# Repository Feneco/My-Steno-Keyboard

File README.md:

# My-Steno-Keyboard
A small stenography keyboard project, including kicad files

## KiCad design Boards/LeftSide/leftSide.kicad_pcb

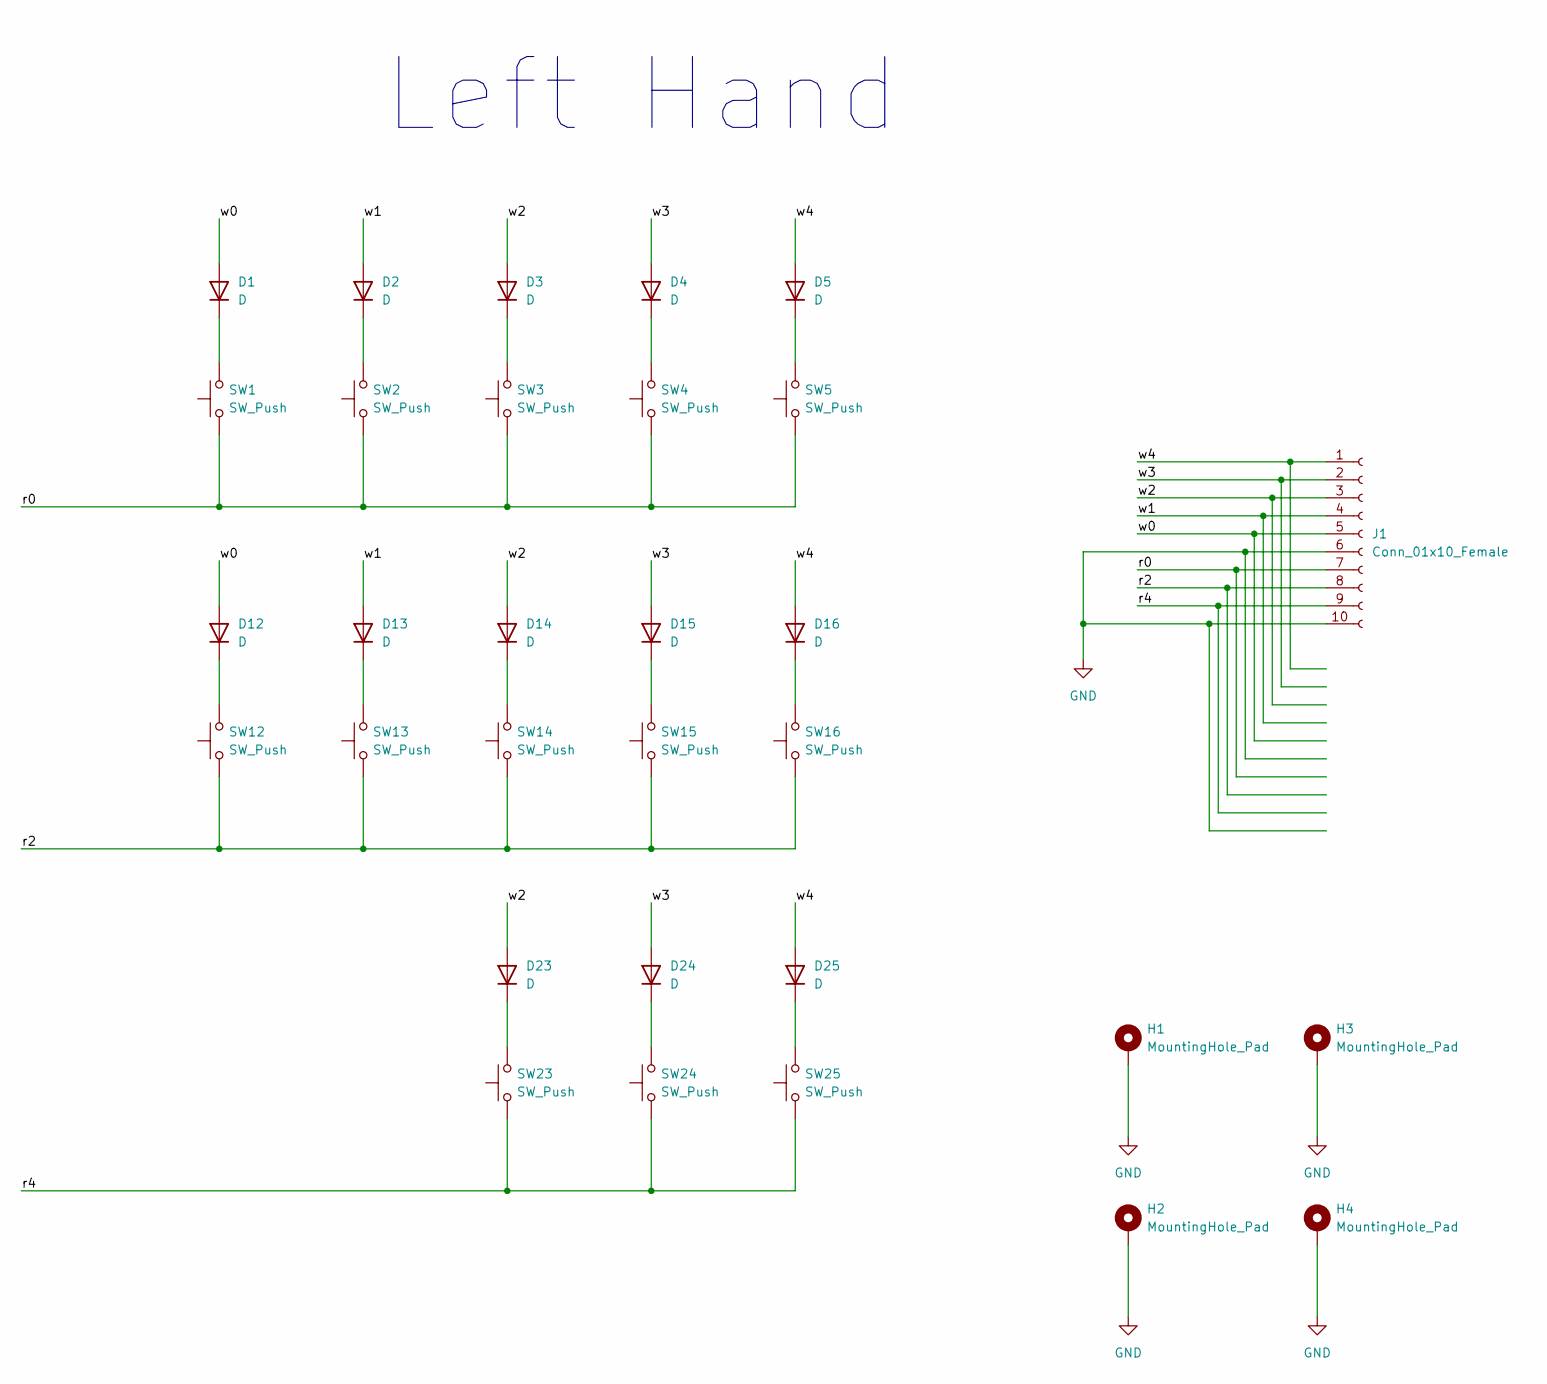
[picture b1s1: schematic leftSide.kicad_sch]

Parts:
D1, D2, D3, D4, D5, D12, D13, D14, D15, D16, D23, D24, D25: D; D_T-1_P5.08mm_Horizontal
H1, H2, H3, H4: MountingHole_Pad; MountingHole_3.2mm_M3_DIN965_Pad
J1: Conn_01x10_Female; PinHeader_1x10_P1.27mm_Vertical
SW1, SW2, SW3, SW4, SW5, SW12, SW13, SW14, SW15, SW16, SW23, SW24, SW25: SW_Push; SW_Cherry_MX_1.00u_PCB

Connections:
/r0: J1.7, SW1.1, SW2.1, SW3.1, SW4.1, SW5.1
/r2: J1.8, SW12.1, SW13.1, SW14.1, SW15.1, SW16.1
/r4: J1.9, SW23.1, SW24.1, SW25.1
/w0: D1.2 (A), D12.2 (A), J1.5
/w1: D2.2 (A), D13.2 (A), J1.4
/w2: D3.2 (A), D14.2 (A), D23.2 (A), J1.3
/w3: D4.2 (A), D15.2 (A), D24.2 (A), J1.2
/w4: D5.2 (A), D16.2 (A), D25.2 (A), J1.1
GND: H1.1, H2.1, H3.1, H4.1, J1.6, J1.10
unnamed: D1.1 (K), SW1.2
unnamed: D2.1 (K), SW2.2
unnamed: D3.1 (K), SW3.2
unnamed: D4.1 (K), SW4.2
unnamed: D5.1 (K), SW5.2
unnamed: D12.1 (K), SW12.2
unnamed: D13.1 (K), SW13.2
unnamed: D14.1 (K), SW14.2
unnamed: D15.1 (K), SW15.2
unnamed: D16.1 (K), SW16.2
unnamed: D23.1 (K), SW23.2
unnamed: D24.1 (K), SW24.2
unnamed: D25.1 (K), SW25.2

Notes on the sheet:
Left Hand

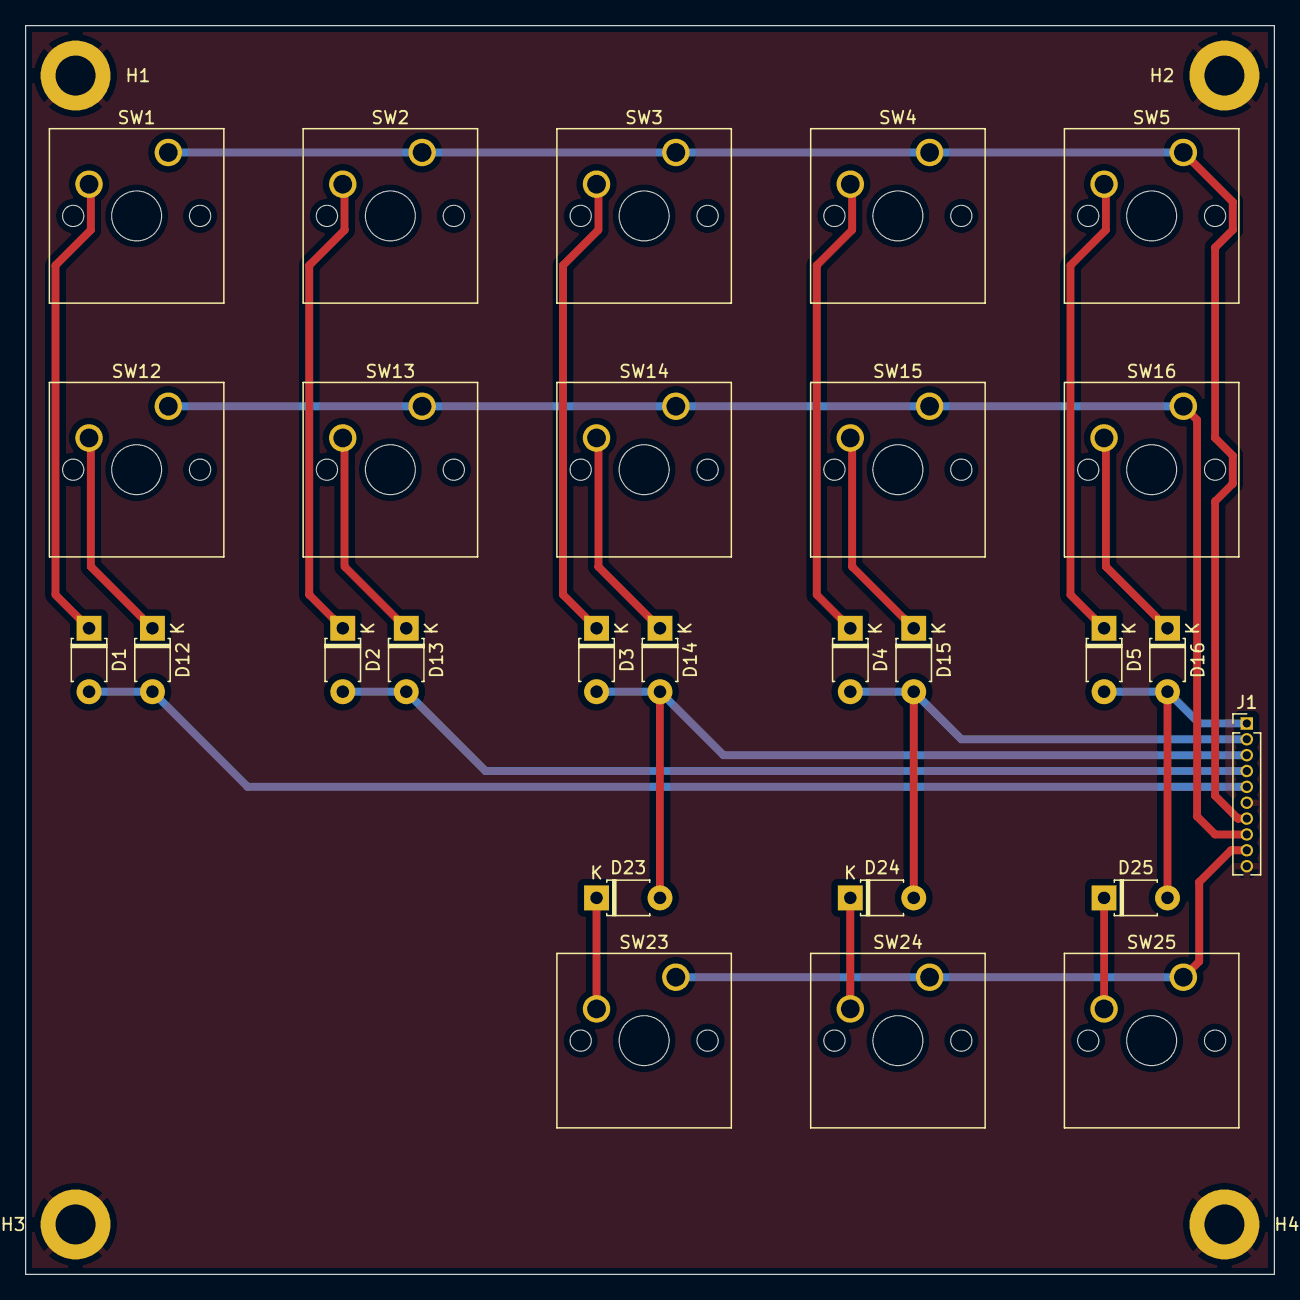
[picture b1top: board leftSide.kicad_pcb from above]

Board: 2 copper layers, 100.0 x 100.0 mm, 31 parts (0 on the bottom side), 22 nets.

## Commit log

2022-09-10 First commit: Gitignore
2022-09-10 Kicad files
2022-09-10 added image
